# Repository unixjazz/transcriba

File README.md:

# Transcriba 0.4

Integrates VLC media player with an arduino-based USB pedal for audio
transcription.
 
This script is based on Jeffrey Ness' [raw keyboad access
code](https://github.com/jness).  It was inspired and re-written from
'vlccontrol' by [Derek
Barnett](https://wiki.videolan.org/How_to_use_VLC_for_transcription_in_linux).
It uses Al's [Pyperclip](https://pypi.python.org/pypi/pyperclip/1.5.1) for the
usage of the clipboard function on Mac, Windoze, and Linux.
 
Tested with the PRO MICRO Leonardo-compatible board. Here is the pinout: (it 
works with other Leonardo-compatible boards, Teensy, etc.)

```
Pin     Key Assignment            Function
------------------------------------------------
D02     KEY_LEFTCTRL + KEY_F7     Pause/Play 
D03     KEY_LEFTCTRL + KEY_F8     Get Timecode
D04     KEY_LEFTCTRL + KEY_F9     Jump Forward 
D05     KEY_LEFTCTRL + KEY_F10    Jump Backward
D06     KEY_LEFTCTRL + KEY_F11    Speed-Up  
D07     KEY_LEFTCTRL + KEY_F12    Slow-Down
```

## Getting Started

You need to configure VLC before using the script:

* Open VLC: preferences: advanced preferences and configure its interface to 
use 'RC', check the option 'fake tty' and 'UNIX socket command input' to 
the path of the script;
 
* Open 'keyboard.map' for a list of keycodes. Edit transcriba.py and change the
keycodes according to your environment;

* Plug your USB pedal and launch the script.

## Assembly Instructions

The prototype was based on a L-shaped aluminum bar (which can be found in any
hardware store), a collection of buttons, wires, and an ATmega32U4 MCU (which
can be found in many projects, most notably on the Arduino Leonardo):

[Pedal Transcriba prototype](pedal_0.1.jpg)

TODO: describe the assembly process w/ the PCB, as soon as it is ready!

## Licensing

Each dependency has specific licensing requirements. Check their respective
files for further information.  This script is distributed under the GPL
version 2. For further information, read 'LICENSE'.

*Enjoy Transcribing!*
 (just kidding...)

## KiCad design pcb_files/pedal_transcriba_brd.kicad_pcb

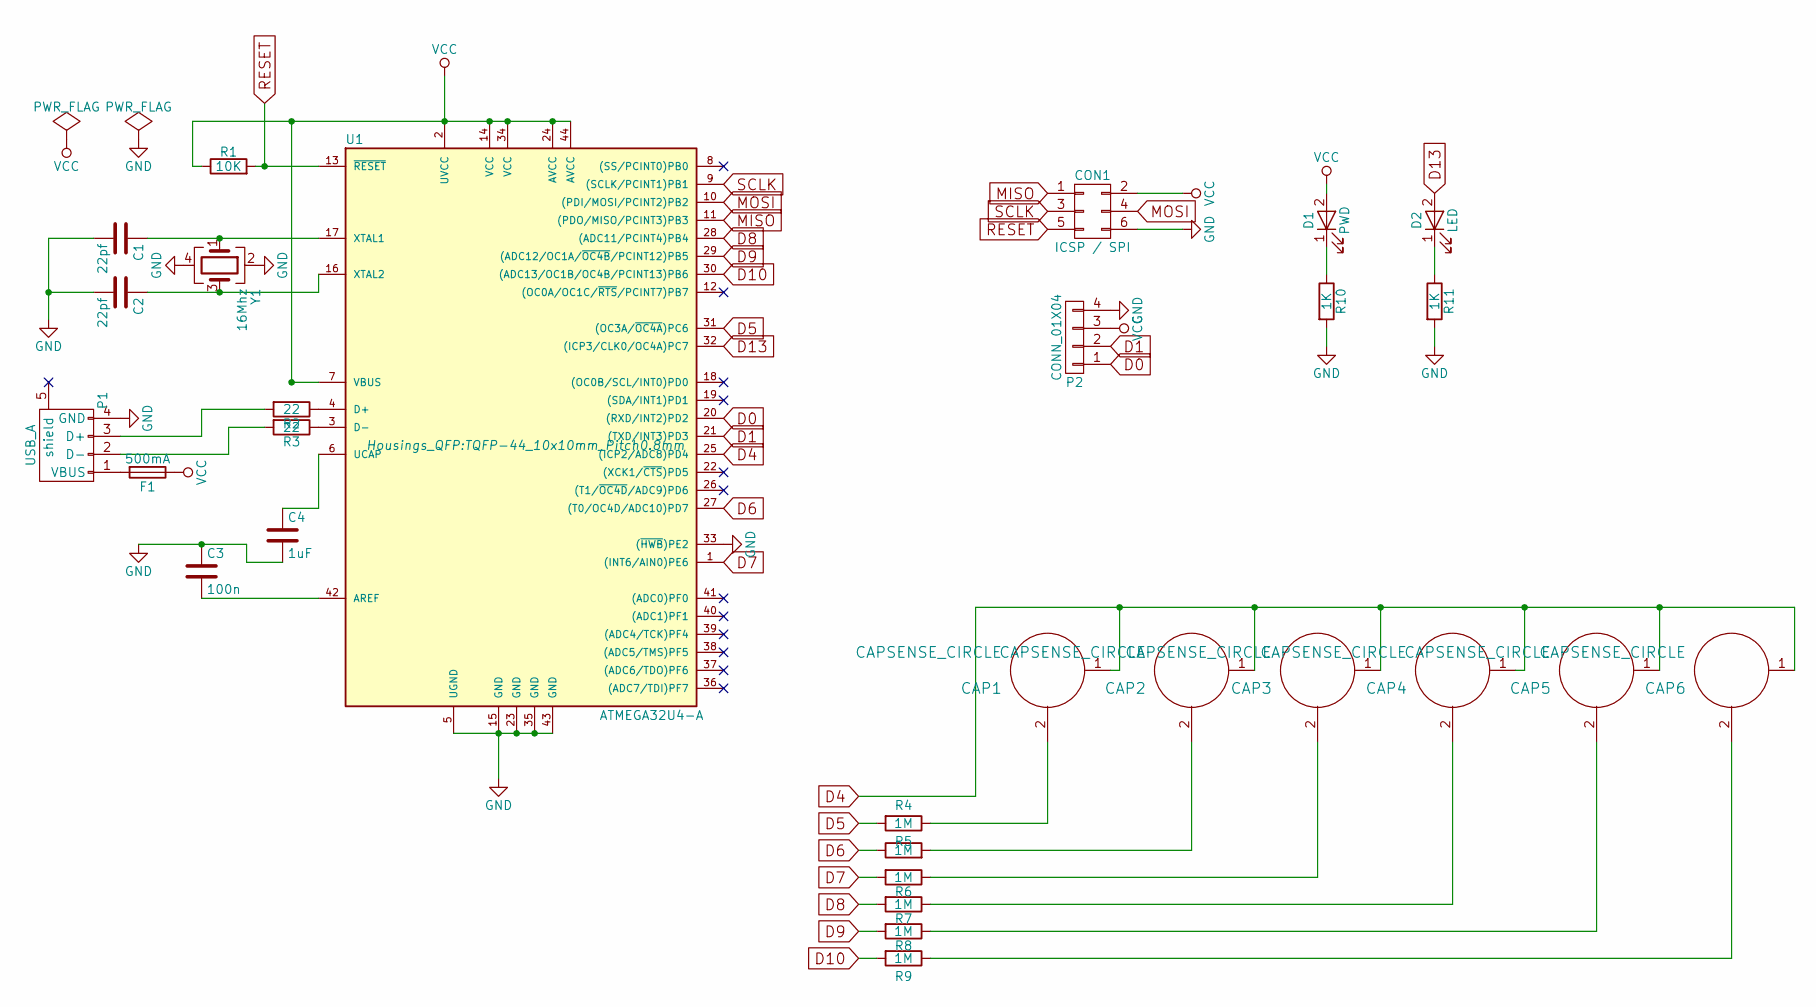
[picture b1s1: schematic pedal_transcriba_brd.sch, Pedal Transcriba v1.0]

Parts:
C1, C2: 22pf; C_0201
C3: 100n; C_0201
C4: 1uF; C_0201
CAP1, CAP2, CAP3, CAP4, CAP5, CAP6: CAPSENSE_CIRCLE; CAPSENSE-CIRCLE-D10MM-MOD
CON1: ICSP / SPI; Pin_Header_Straight_2x03
D1: PWD; LED_0603
D2: LED; LED_0603
F1: 500mA; Fuse_SMD1206_Reflow
P1: USB_A; USB_Micro-B_10103594-0001LF
P2: CONN_01X04; Pin_Header_Straight_1x04
R1: 10K; R_0201
R2, R3: 22; R_0201
R4, R5, R6, R7, R8, R9: 1M; R_0201
R10, R11: 1K; R_0201
U1: ATMEGA32U4-A; TQFP-44_10x10mm_Pitch0.8mm
Y1: 16Mhz; Crystal_SMD_Abracon_ABM3B-4pin_5.0x3.2mm

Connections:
D0: P2.1, U1.20 ((RXD/INT2)PD2)
D1: P2.2, U1.21 ((TXD/INT3)PD3)
D4: CAP1.1 (BUTTON), CAP2.1 (BUTTON), CAP3.1 (BUTTON), CAP4.1 (BUTTON), CAP5.1 (BUTTON), CAP6.1 (BUTTON), U1.25 ((ICP2/ADC8)PD4)
D5: R4.2, U1.31 ((OC3A/~OC4A~)PC6)
D6: R5.1, U1.27 ((T0/OC4D/ADC10)PD7)
D7: R6.2, U1.1 ((INT6/AIN0)PE6)
D8: R7.2, U1.28 ((ADC11/PCINT4)PB4)
D9: R8.2, U1.29 ((ADC12/OC1A/~OC4B~/PCINT12)PB5)
D10: R9.2, U1.30 ((ADC13/OC1B/OC4B/PCINT13)PB6)
D13: D2.2 (A), U1.32 ((ICP3/CLK0/OC4A)PC7)
GND: C1.2, C2.2, C3.1, C4.2, CON1.6, P1.4 (GND), P2.4, R10.2, R11.2, U1.5 (UGND), U1.15 (GND), U1.23 (GND), U1.33 ((~HWB~)PE2), U1.35 (GND), U1.43 (GND), Y1.2, Y1.4
MISO: CON1.1, U1.11 ((PDO/MISO/PCINT3)PB3)
MOSI: CON1.4, U1.10 ((PDI/MOSI/PCINT2)PB2)
unnamed: C1.1, U1.17 (XTAL1), Y1.1
unnamed: C2.1, U1.16 (XTAL2), Y1.3
unnamed: C3.2, U1.42 (AREF)
unnamed: C4.1, U1.6 (UCAP)
unnamed: CAP1.2, R4.1
unnamed: CAP2.2, R5.2
unnamed: CAP3.2, R6.1
unnamed: CAP4.2, R7.1
unnamed: CAP5.2, R8.1
unnamed: CAP6.2, R9.1
unnamed 23: D1.1 (K), R10.1; also elsewhere on the board
unnamed: D2.1 (K), R11.1
unnamed: F1.2, P1.1 (VBUS)
unnamed: P1.2 (D-), R3.2
unnamed: P1.3 (D+), R2.2
unnamed: R2.1, U1.4 (D+)
unnamed: R3.1, U1.3 (D-)
RESET: CON1.5, R1.2, U1.13 (~RESET~)
SCLK: CON1.3, U1.9 ((SCLK/PCINT1)PB1)
VCC: CON1.2, D1.2 (A), F1.1, P2.3, R1.1, U1.2 (UVCC), U1.7 (VBUS), U1.14 (VCC), U1.24 (AVCC), U1.34 (VCC), U1.44 (AVCC); also elsewhere on the board

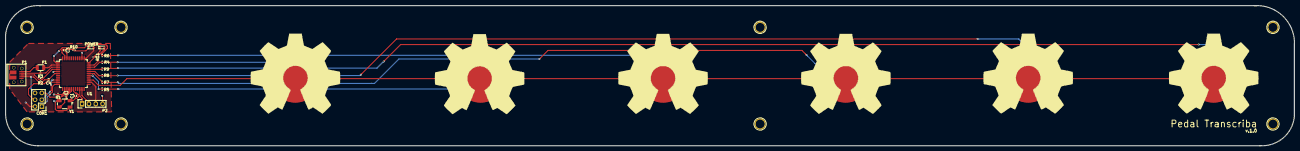
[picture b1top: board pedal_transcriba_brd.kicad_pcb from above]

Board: 2 copper layers, 480.0 x 52.2 mm, 28 parts (0 on the bottom side), 31 nets.

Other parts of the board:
POWER: PWD; LED_0603

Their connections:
unnamed 23: POWER.1; also elsewhere on the board
VCC: POWER.2; also elsewhere on the board

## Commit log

2015-02-09 adding files
2015-02-09 adding Leonardo firmware file
2015-02-12 update python xaut
2017-03-07 adding pedal prototype image
2017-08-21 updated README file.
2017-08-21 added PyQt version of the script + KiCad design files.
2017-08-21 removing dep files from old script.

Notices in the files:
pcb_files/pedal_transcriba_brd.kicad_pcb:
by Unixjazz --- l: CERN OHL 1.2
pcb_files/pedal_transcriba_brd.sch:
Licensed with CERN OHL 1.2 by 'unixjazz'
